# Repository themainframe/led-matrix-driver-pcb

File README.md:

# led-matrix-driver-pcb

This is the CAM repository for my LED Matrix Driver Project based on ESP32.

The files are in KiCAD EDA format.

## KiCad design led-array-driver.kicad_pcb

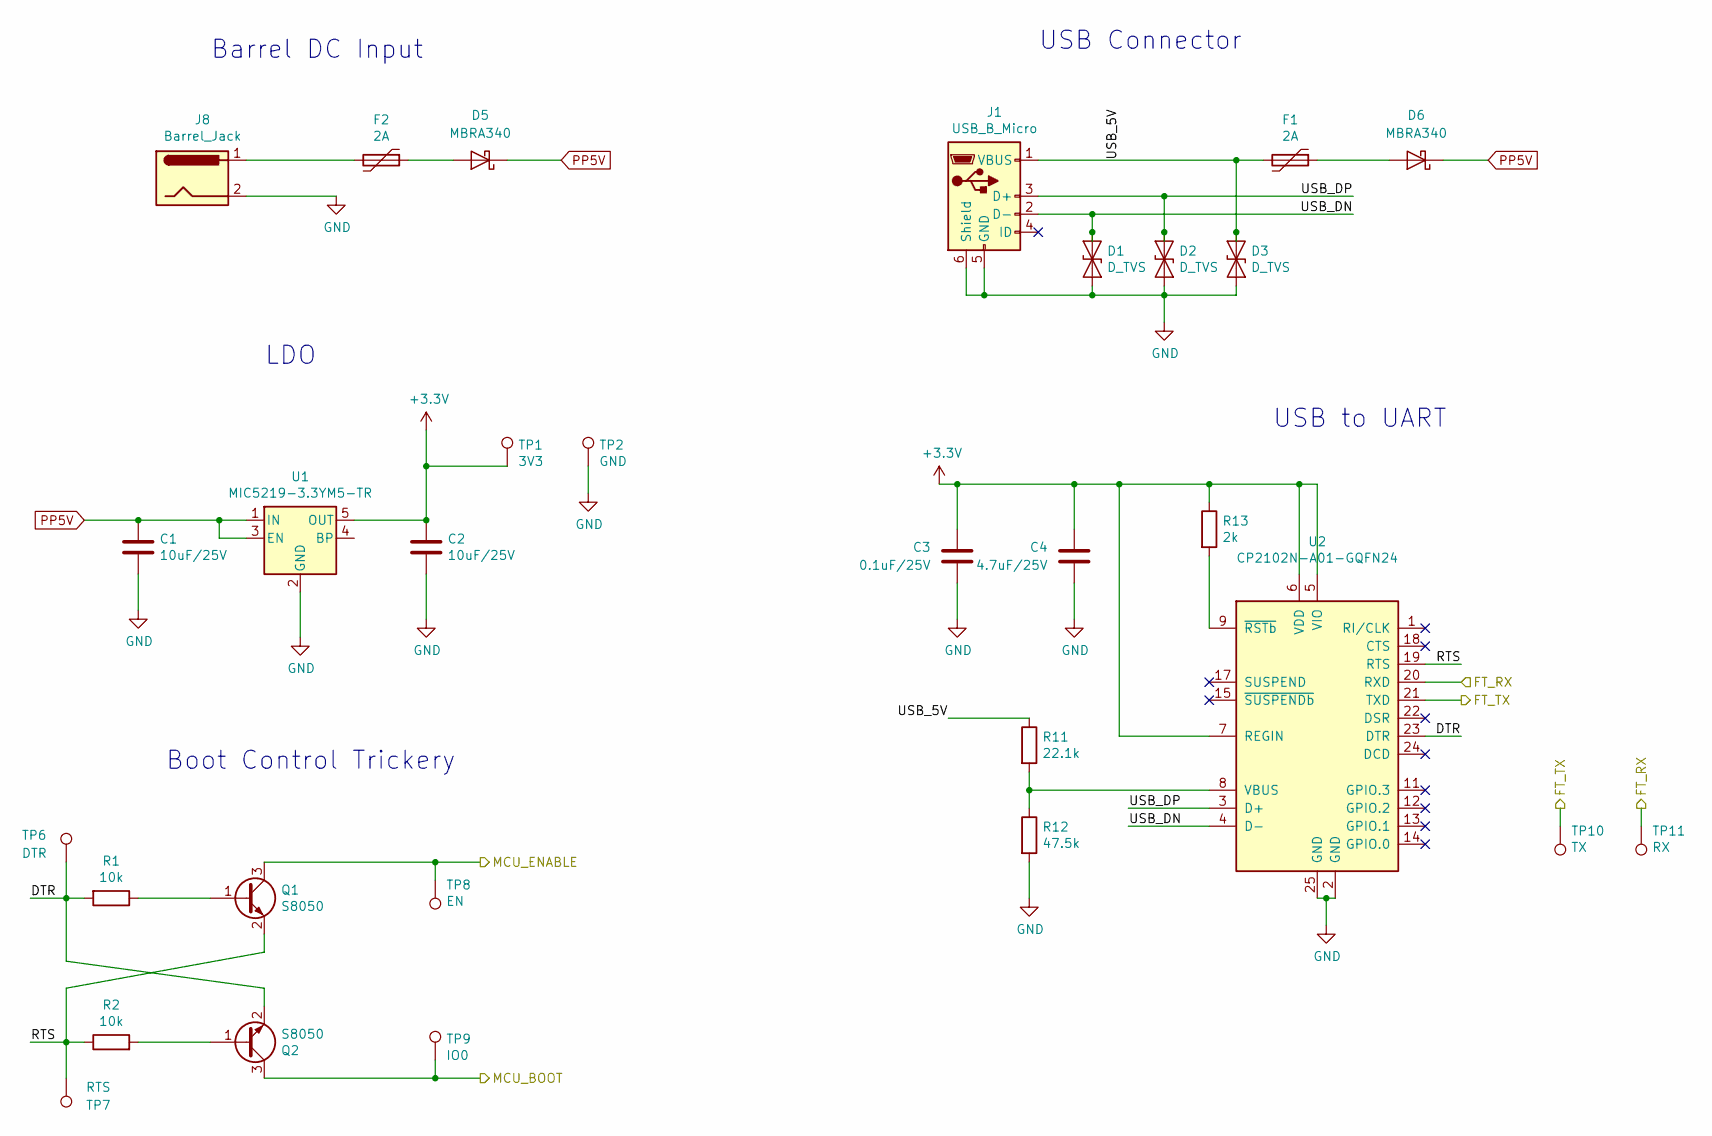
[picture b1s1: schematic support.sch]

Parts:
C1, C2: 10uF/25V; C_0805_2012Metric
C3: 0.1uF/25V; C_0603_1608Metric
C4: 4.7uF/25V; C_0805_2012Metric
D1, D2, D3: D_TVS; D_0603_1608Metric
D5, D6: MBRA340; D_SMA
F1, F2: 2A; Bourns_MF-MSMF260-2_Polyfuse_2.6A
J1: USB_B_Micro; USB_Micro-B_Molex-105017-0001
J8: Barrel_Jack; BarrelJack_Wuerth_6941xx301002
Q1, Q2: S8050; SOT-23
R1, R2: 10k; R_0603_1608Metric
R11: 22.1k; R_0603_1608Metric
R12: 47.5k; R_0603_1608Metric
R13: 2k; R_0603_1608Metric
TP1: 3V3; TestPoint_Pad_D1.0mm
TP2: GND; TestPoint_Pad_D1.0mm
TP6: DTR; TestPoint_Pad_D1.0mm
TP7: RTS; TestPoint_Pad_D1.0mm
TP8: EN; TestPoint_Pad_D1.0mm
TP9: IO0; TestPoint_Pad_D1.0mm
TP10: TX; TestPoint_Pad_D1.0mm
TP11: RX; TestPoint_Pad_D1.0mm
U1: MIC5219-3.3YM5-TR; SOT-23-5
U2: CP2102N-A01-GQFN24; QFN-24-1EP_4x4mm_P0.5mm_EP2.6x2.6mm

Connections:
+3V3: C2.1, C3.1, C4.1, R13.1, TP1.1, U1.5 (OUT), U2.5 (VIO), U2.6 (VDD), U2.7 (REGIN); also elsewhere on the board
/ESP32/ESP_RX: TP10.1, U2.21 (TXD); also elsewhere on the board
/ESP32/ESP_TX: TP11.1, U2.20 (RXD); also elsewhere on the board
/ESP32/MCU_BOOT: Q2.3 (C), TP9.1; also elsewhere on the board
/ESP32/MCU_ENABLE: Q1.3 (C), TP8.1; also elsewhere on the board
/Support Circuitry/DTR: Q2.2 (E), R1.2, TP6.1, U2.23 (DTR)
/Support Circuitry/RTS: Q1.2 (E), R2.1, TP7.1, U2.19 (RTS)
/Support Circuitry/USB_5V: D3.1 (A1), F1.2, J1.1 (VBUS), R11.1
/Support Circuitry/USB_DN: D1.1 (A1), J1.2 (D-), U2.4 (D-)
/Support Circuitry/USB_DP: D2.1 (A1), J1.3 (D+), U2.3 (D+)
GND: C1.2, C2.2, C3.2, C4.2, D1.2 (A2), D2.2 (A2), D3.2 (A2), J1.5 (GND), J1.6 (Shield), J8.2, R12.2, TP2.1, U1.2 (GND), U2.2 (GND), U2.25 (GND); also elsewhere on the board
unnamed: D5.2 (A), F2.1
unnamed: D6.2 (A), F1.1
unnamed: F2.2, J8.1
unnamed: Q1.1 (B), R1.1
unnamed: Q2.1 (B), R2.2
unnamed: R11.2, R12.1, U2.8 (VBUS)
unnamed: R13.2, U2.9 (~RSTb)
PP5V: C1.1, D5.1 (K), D6.1 (K), U1.1 (IN), U1.3 (EN); also elsewhere on the board

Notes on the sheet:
LDO
USB Connector
Boot Control Trickery
USB to UART
Barrel DC Input

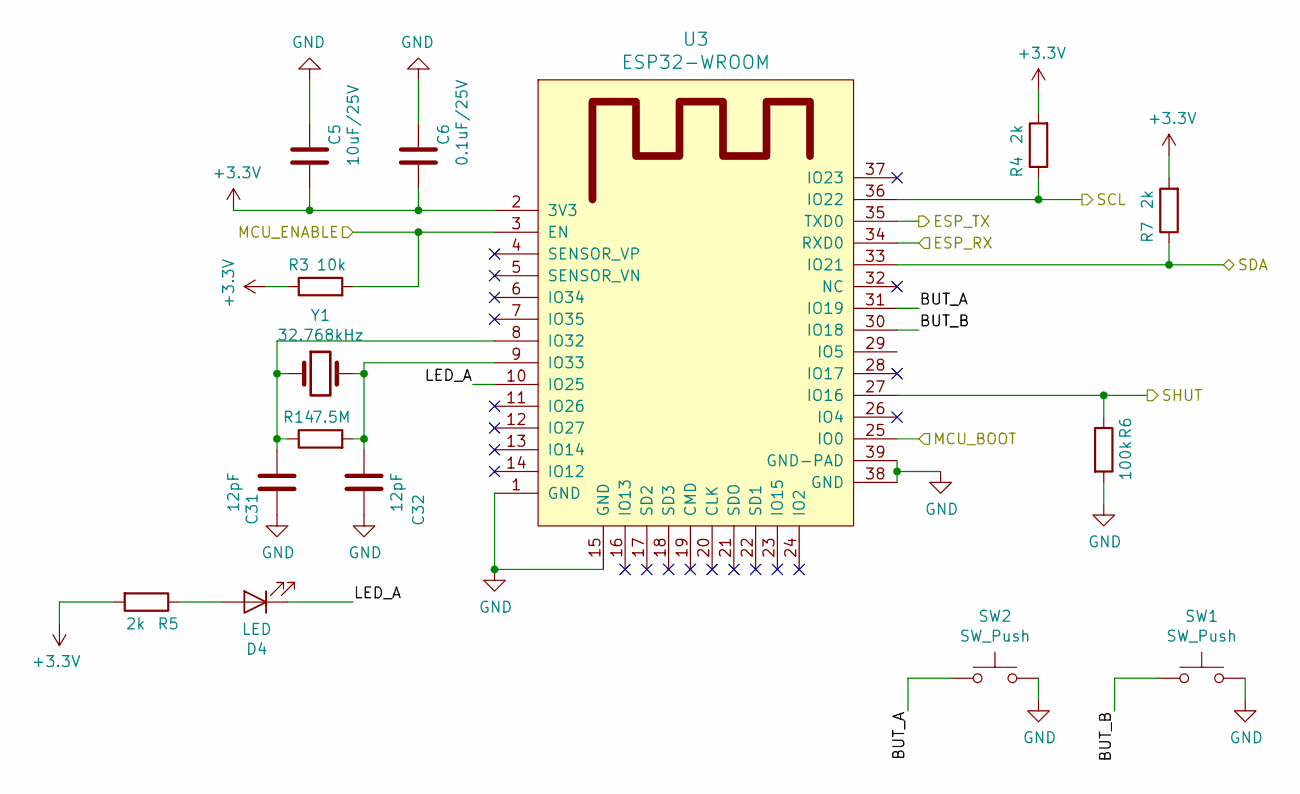
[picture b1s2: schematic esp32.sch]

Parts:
C5: 10uF/25V; C_0805_2012Metric
C6: 0.1uF/25V; C_0603_1608Metric
C31, C32: 12pF; C_0603_1608Metric
D4: LED; LED_0805_2012Metric
R3: 10k; R_0603_1608Metric
R4, R5, R7: 2k; R_0603_1608Metric
R6: 100k; R_0603_1608Metric
R14: 7.5M; R_0603_1608Metric
SW1, SW2: SW_Push; SW_SPST_EVQP7A
U3: ESP32-WROOM; ESP32-WROOM-32
Y1: 32.768kHz; Crystal_SMD_MicroCrystal_CC7V-T1A-2Pin_3.2x1.5mm

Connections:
+3V3: C5.2, C6.2, R3.1, R4.2, R5.2, R7.2, U3.2 (3V3); also elsewhere on the board
/Drivers/SCL: R4.1, U3.36 (IO22); also elsewhere on the board
/Drivers/SDA: R7.1, U3.33 (IO21); also elsewhere on the board
/Drivers/SHUT: R6.1, U3.27 (IO16); also elsewhere on the board
/ESP32/BUT_A: SW2.1, U3.31 (IO19)
/ESP32/BUT_B: SW1.1, U3.30 (IO18)
/ESP32/ESP_RX: U3.34 (RXD0); also elsewhere on the board
/ESP32/ESP_TX: U3.35 (TXD0); also elsewhere on the board
/ESP32/LED_A: D4.1 (K), U3.10 (IO25)
/ESP32/MCU_BOOT: U3.25 (IO0); also elsewhere on the board
/ESP32/MCU_ENABLE: R3.2, U3.3 (EN); also elsewhere on the board
GND: C5.1, C6.1, C31.1, C32.1, R6.2, SW1.2, SW2.2, U3.1 (GND), U3.15 (GND), U3.38 (GND), U3.39 (GND-PAD); also elsewhere on the board
unnamed: C31.2, R14.1, U3.8 (IO32), Y1.1
unnamed: C32.2, R14.2, U3.9 (IO33), Y1.2
unnamed: D4.2 (A), R5.1

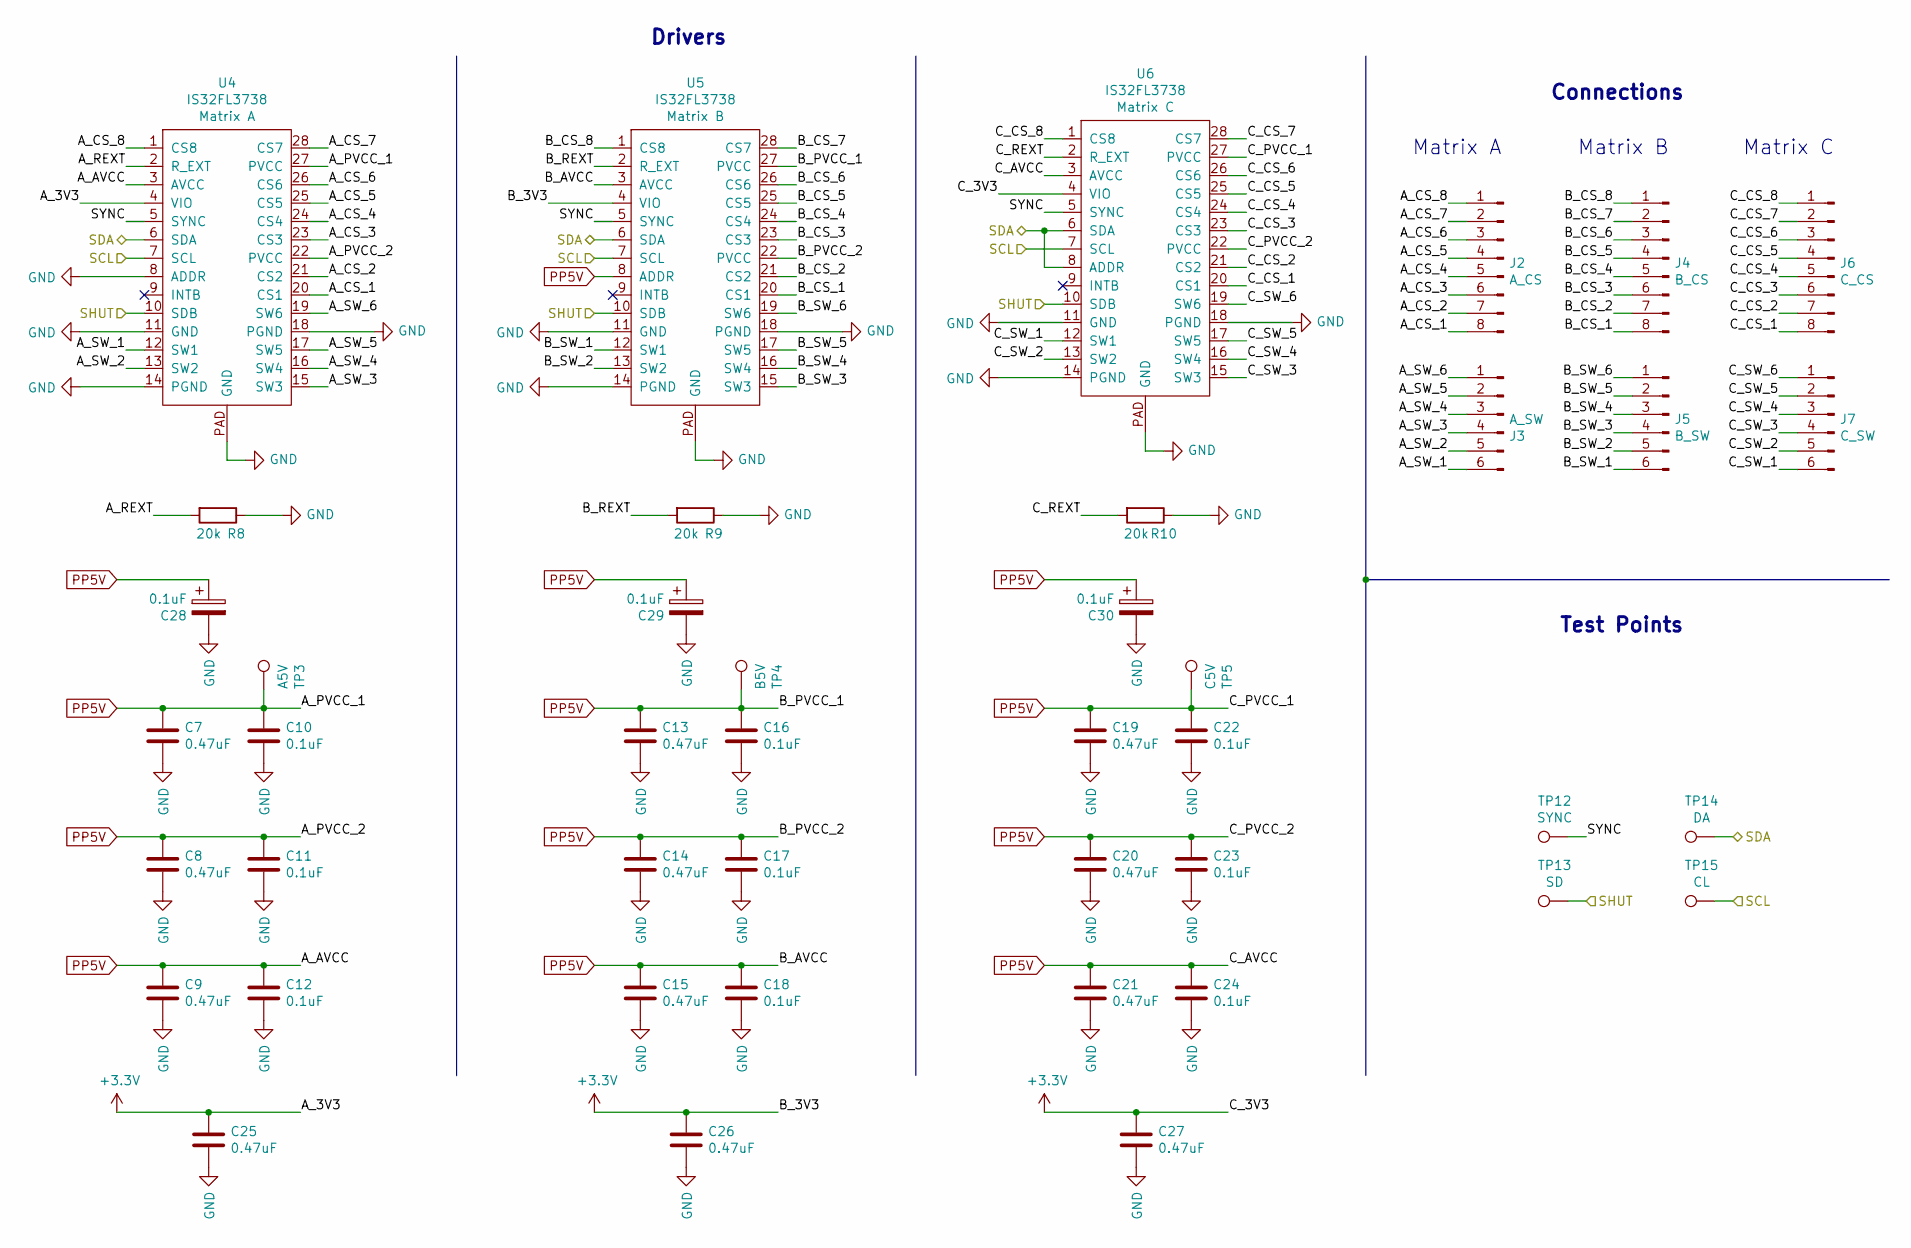
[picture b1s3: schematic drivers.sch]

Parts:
C7, C8, C9, C13, C14, C15, C19, C20, C21, C25, C26, C27: 0.47uF; C_0603_1608Metric
C10, C11, C12, C16, C17, C18, C22, C23, C24: 0.1uF; C_0603_1608Metric
C28, C29, C30: 0.1uF; CP_Elec_5x5.4
J2: A_CS; PinHeader_1x08_P2.54mm_Horizontal
J3: A_SW; PinHeader_1x06_P2.54mm_Horizontal
J4: B_CS; PinHeader_1x08_P2.54mm_Horizontal
J5: B_SW; PinHeader_1x06_P2.54mm_Horizontal
J6: C_CS; PinHeader_1x08_P2.54mm_Horizontal
J7: C_SW; PinHeader_1x06_P2.54mm_Horizontal
R8, R9, R10: 20k; R_0603_1608Metric
TP3: A5V; TestPoint_Pad_D1.0mm
TP4: B5V; TestPoint_Pad_D1.0mm
TP5: C5V; TestPoint_Pad_D1.0mm
TP12: SYNC; TestPoint_Pad_D1.0mm
TP13: SD; TestPoint_Pad_D1.0mm
TP14: DA; TestPoint_Pad_D1.0mm
TP15: CL; TestPoint_Pad_D1.0mm
U4, U5, U6: IS32FL3738; SOP65P640X110-28N

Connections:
+3V3: C25.2, C26.2, C27.2, U4.4 (VIO), U5.4 (VIO), U6.4 (VIO); also elsewhere on the board
/Drivers/A_CS_1: J2.8, U4.20 (CS1)
/Drivers/A_CS_2: J2.7, U4.21 (CS2)
/Drivers/A_CS_3: J2.6, U4.23 (CS3)
/Drivers/A_CS_4: J2.5, U4.24 (CS4)
/Drivers/A_CS_5: J2.4, U4.25 (CS5)
/Drivers/A_CS_6: J2.3, U4.26 (CS6)
/Drivers/A_CS_7: J2.2, U4.28 (CS7)
/Drivers/A_CS_8: J2.1, U4.1 (CS8)
/Drivers/A_REXT: R8.2, U4.2 (R_EXT)
/Drivers/A_SW_1: J3.6, U4.12 (SW1)
/Drivers/A_SW_2: J3.5, U4.13 (SW2)
/Drivers/A_SW_3: J3.4, U4.15 (SW3)
/Drivers/A_SW_4: J3.3, U4.16 (SW4)
/Drivers/A_SW_5: J3.2, U4.17 (SW5)
/Drivers/A_SW_6: J3.1, U4.19 (SW6)
/Drivers/B_CS_1: J4.8, U5.20 (CS1)
/Drivers/B_CS_2: J4.7, U5.21 (CS2)
/Drivers/B_CS_3: J4.6, U5.23 (CS3)
/Drivers/B_CS_4: J4.5, U5.24 (CS4)
/Drivers/B_CS_5: J4.4, U5.25 (CS5)
/Drivers/B_CS_6: J4.3, U5.26 (CS6)
/Drivers/B_CS_7: J4.2, U5.28 (CS7)
/Drivers/B_CS_8: J4.1, U5.1 (CS8)
/Drivers/B_REXT: R9.2, U5.2 (R_EXT)
/Drivers/B_SW_1: J5.6, U5.12 (SW1)
/Drivers/B_SW_2: J5.5, U5.13 (SW2)
/Drivers/B_SW_3: J5.4, U5.15 (SW3)
/Drivers/B_SW_4: J5.3, U5.16 (SW4)
/Drivers/B_SW_5: J5.2, U5.17 (SW5)
/Drivers/B_SW_6: J5.1, U5.19 (SW6)
/Drivers/C_CS_1: J6.8, U6.20 (CS1)
/Drivers/C_CS_2: J6.7, U6.21 (CS2)
/Drivers/C_CS_3: J6.6, U6.23 (CS3)
/Drivers/C_CS_4: J6.5, U6.24 (CS4)
/Drivers/C_CS_5: J6.4, U6.25 (CS5)
/Drivers/C_CS_6: J6.3, U6.26 (CS6)
/Drivers/C_CS_7: J6.2, U6.28 (CS7)
/Drivers/C_CS_8: J6.1, U6.1 (CS8)
/Drivers/C_REXT: R10.2, U6.2 (R_EXT)
/Drivers/C_SW_1: J7.6, U6.12 (SW1)
/Drivers/C_SW_2: J7.5, U6.13 (SW2)
/Drivers/C_SW_3: J7.4, U6.15 (SW3)
/Drivers/C_SW_4: J7.3, U6.16 (SW4)
/Drivers/C_SW_5: J7.2, U6.17 (SW5)
/Drivers/C_SW_6: J7.1, U6.19 (SW6)
/Drivers/SCL: TP15.1, U4.7 (SCL), U5.7 (SCL), U6.7 (SCL); also elsewhere on the board
/Drivers/SDA: TP14.1, U4.6 (SDA), U5.6 (SDA), U6.6 (SDA), U6.8 (ADDR); also elsewhere on the board
/Drivers/SHUT: TP13.1, U4.10 (SDB), U5.10 (SDB), U6.10 (SDB); also elsewhere on the board
/Drivers/SYNC: TP12.1, U4.5 (SYNC), U5.5 (SYNC), U6.5 (SYNC)
GND: C7.1, C8.1, C9.1, C10.1, C11.1, C12.1, C13.1, C14.1, C15.1, C16.1, C17.1, C18.1, C19.1, C20.1, C21.1, C22.1, C23.1, C24.1, C25.1, C26.1, C27.1, C28.2, C29.2, C30.2, R8.1, R9.1, R10.1, U4.8 (ADDR), U4.11 (GND), U4.14 (PGND), U4.18 (PGND), U4.PAD (GND), U5.11 (GND), U5.14 (PGND), U5.18 (PGND), U5.PAD (GND), U6.11 (GND), U6.14 (PGND), U6.18 (PGND), U6.PAD (GND); also elsewhere on the board
PP5V: C7.2, C8.2, C9.2, C10.2, C11.2, C12.2, C13.2, C14.2, C15.2, C16.2, C17.2, C18.2, C19.2, C20.2, C21.2, C22.2, C23.2, C24.2, C28.1, C29.1, C30.1, TP3.1, TP4.1, TP5.1, U4.3 (AVCC), U4.22 (PVCC), U4.27 (PVCC), U5.3 (AVCC), U5.8 (ADDR), U5.22 (PVCC), U5.27 (PVCC), U6.3 (AVCC), U6.22 (PVCC), U6.27 (PVCC); also elsewhere on the board

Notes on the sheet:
Matrix A
Matrix B
Matrix C
Connections
Drivers
Test Points

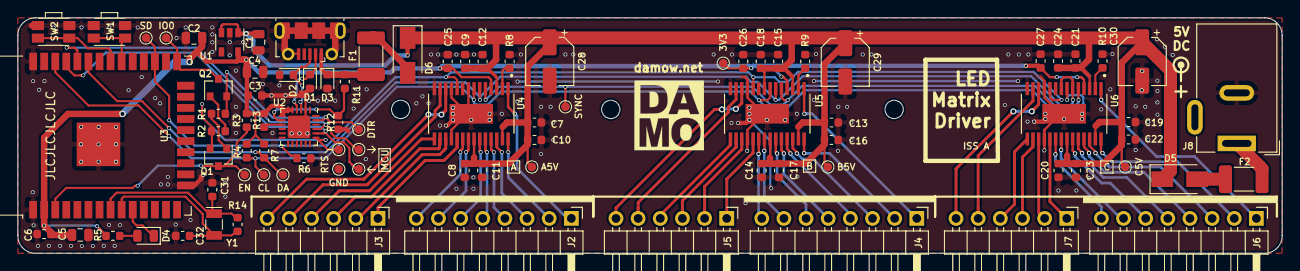
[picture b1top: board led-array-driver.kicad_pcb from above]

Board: 2 copper layers, 145.0 x 27.0 mm, 88 parts (0 on the bottom side), 74 nets.

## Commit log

2020-02-14 Add: Improved layout
2020-02-15 Add: Watch crystal, switches
